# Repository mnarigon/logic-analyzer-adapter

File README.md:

## An S-100 Bus Logic Analyzer Adapter Board.

#### Description

This is an S-100 bus logic analyzer adapter board.
It simplifies the connection to the S-100 bus of common 40-pin pod cables like
those for older HP/Agilent/Keysight logic analyzers.

#### Features:
- Connectors and isolation networks for 40-pin pod cables.
- Oscilloscope test points for S-100 bus signals.
- Test points for logic analyzer clock inputs and unused channels.

See the Keysight document, [Probing Solutions for Logic Analyzers](https://www.keysight.com/us/en/assets/7018-06707/data-sheets/5968-4632.pdf),
for more information on the pod interface.

Note that the photo is of the prototype board.

The design files are revision A, and have some changes based on my experience
with the prototype board. I haven't had the revision A boards manufactured
since the prototype is working for my purposes.

#### Revision A Changes:
- Surface mount components moved to back of board to provide additional
connector clearance.
- Location of pod connectors adjusted to provide more clearance to each other
and to the card ejectors.
- Added test points for unassigned logic analyzer channels.
- Silkscreen for test points moved for visibility.

#### Logic Analyzer Adapter Design Files

The revision A logic analyzer adapter design files in KiCad 7 are in the kicad
directory.

The generated revision A logic analyzer adapter Gerber and drill files are in
the file la-adapter-gerbers.zip.

The bill of materials is in the bom directory.

#### Design Notes

The BOM calls out the 3M connectors described in the Keysight
document. There are probably cheaper, non-3M connectors that would work.

The design files define front and back gold layers to specify hard gold on
the S-100 bus card edge connector. Hard gold is expensive, and few prototype
board houses offer it, so for the prototype I just specified ENIG treatment
for the copper layers and card edge connector.

#### Hand-soldering the Capacitors and Resistors

I use a fine tip soldering iron (Weller with an ETU tip) together with tacky SMD
flux to apply a very light amount of solder to the component pads.
Remove excess solder by reheating with a clean soldering iron and/or using
solder removing wick.
You want just a small pillow of solder on each pad.
After the solder has cooled apply an additional, small amount of flux.
The flux will keep the components in position while they are being soldered with
the hot air rework station.

Then, position the component on the pads using an awl from a desoldering tool
set with a small amount of flux on it.
The tacky flux on the awl will let you transfer and position the component on
the board.

Finally, use a hot air rework station set at a low air velocity to reheat the
solder, flux, and component to solder the component to the board.
Too high an air velocity will blow off the component from the pads.
You can tell when the solder melts because the capillary action of the molten
solder will cause the component to align with the pads.
After the solder melts apply hot air for a slow count of five to ensure that
the flux activates and the solder wets the component and pad.

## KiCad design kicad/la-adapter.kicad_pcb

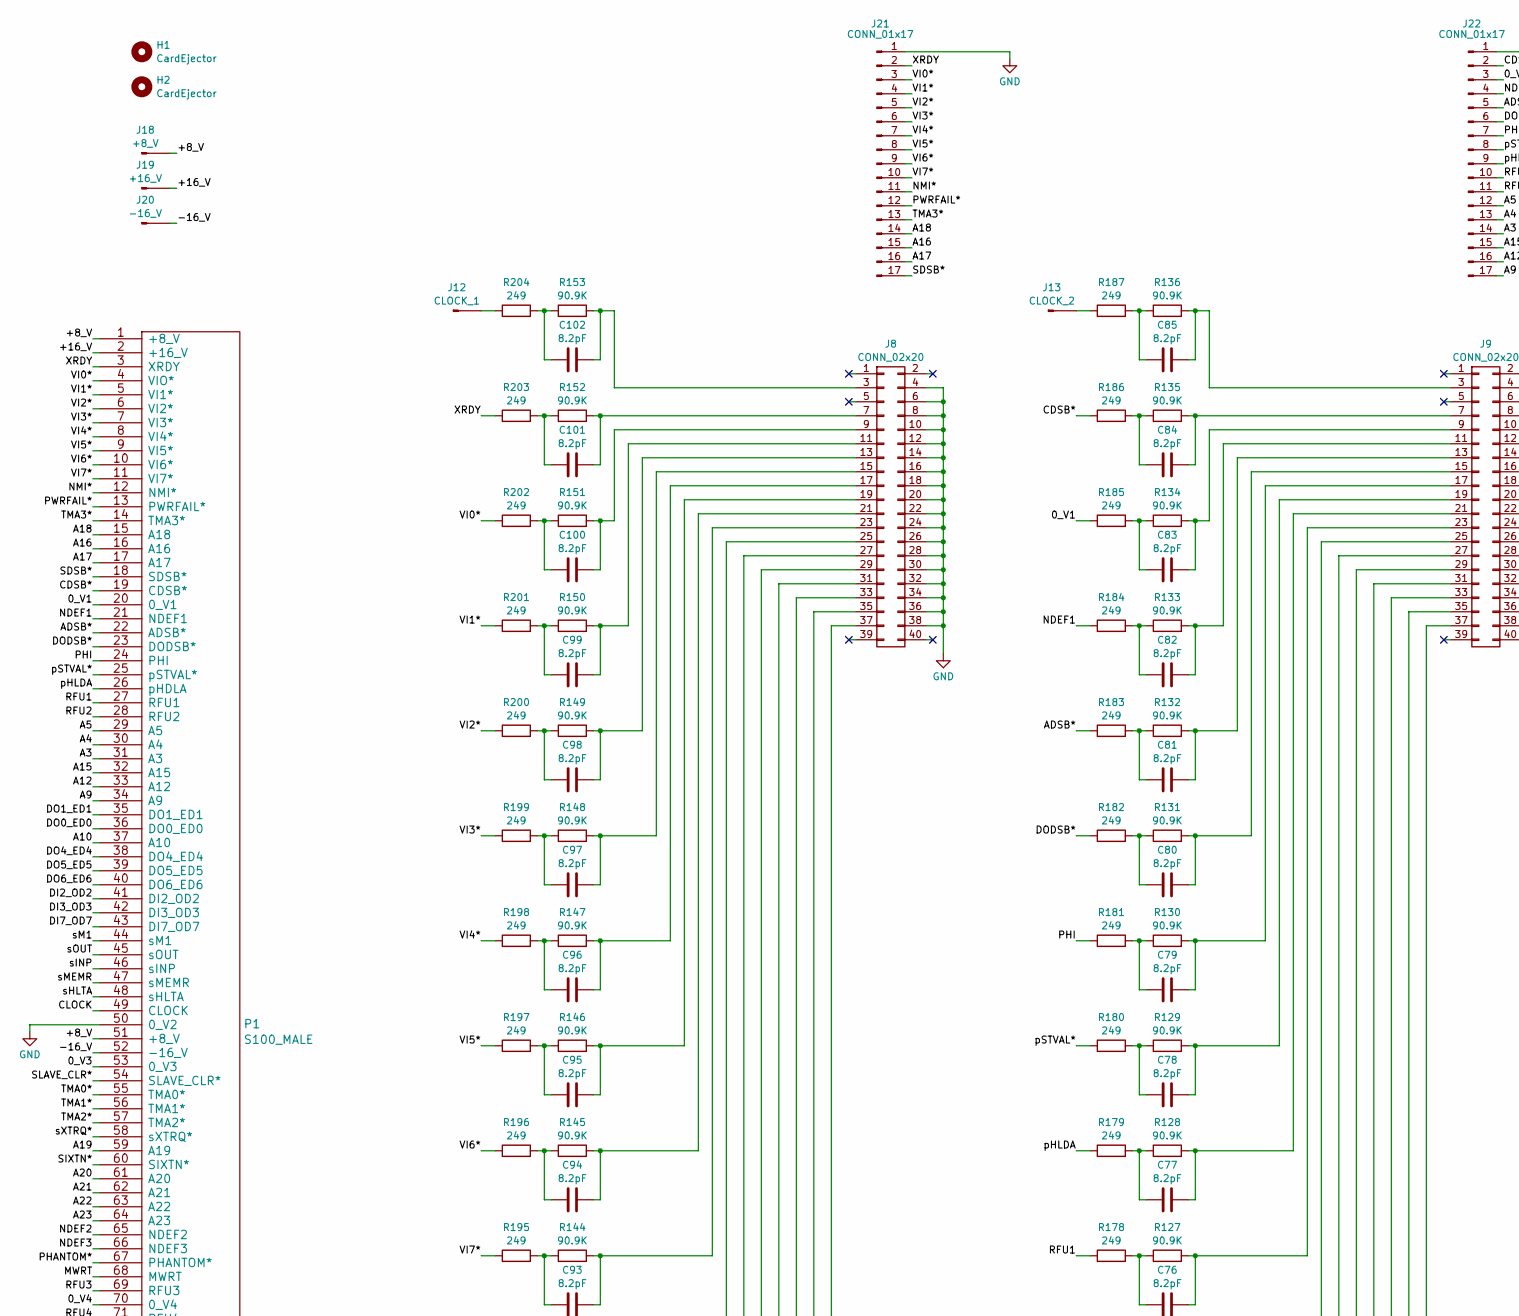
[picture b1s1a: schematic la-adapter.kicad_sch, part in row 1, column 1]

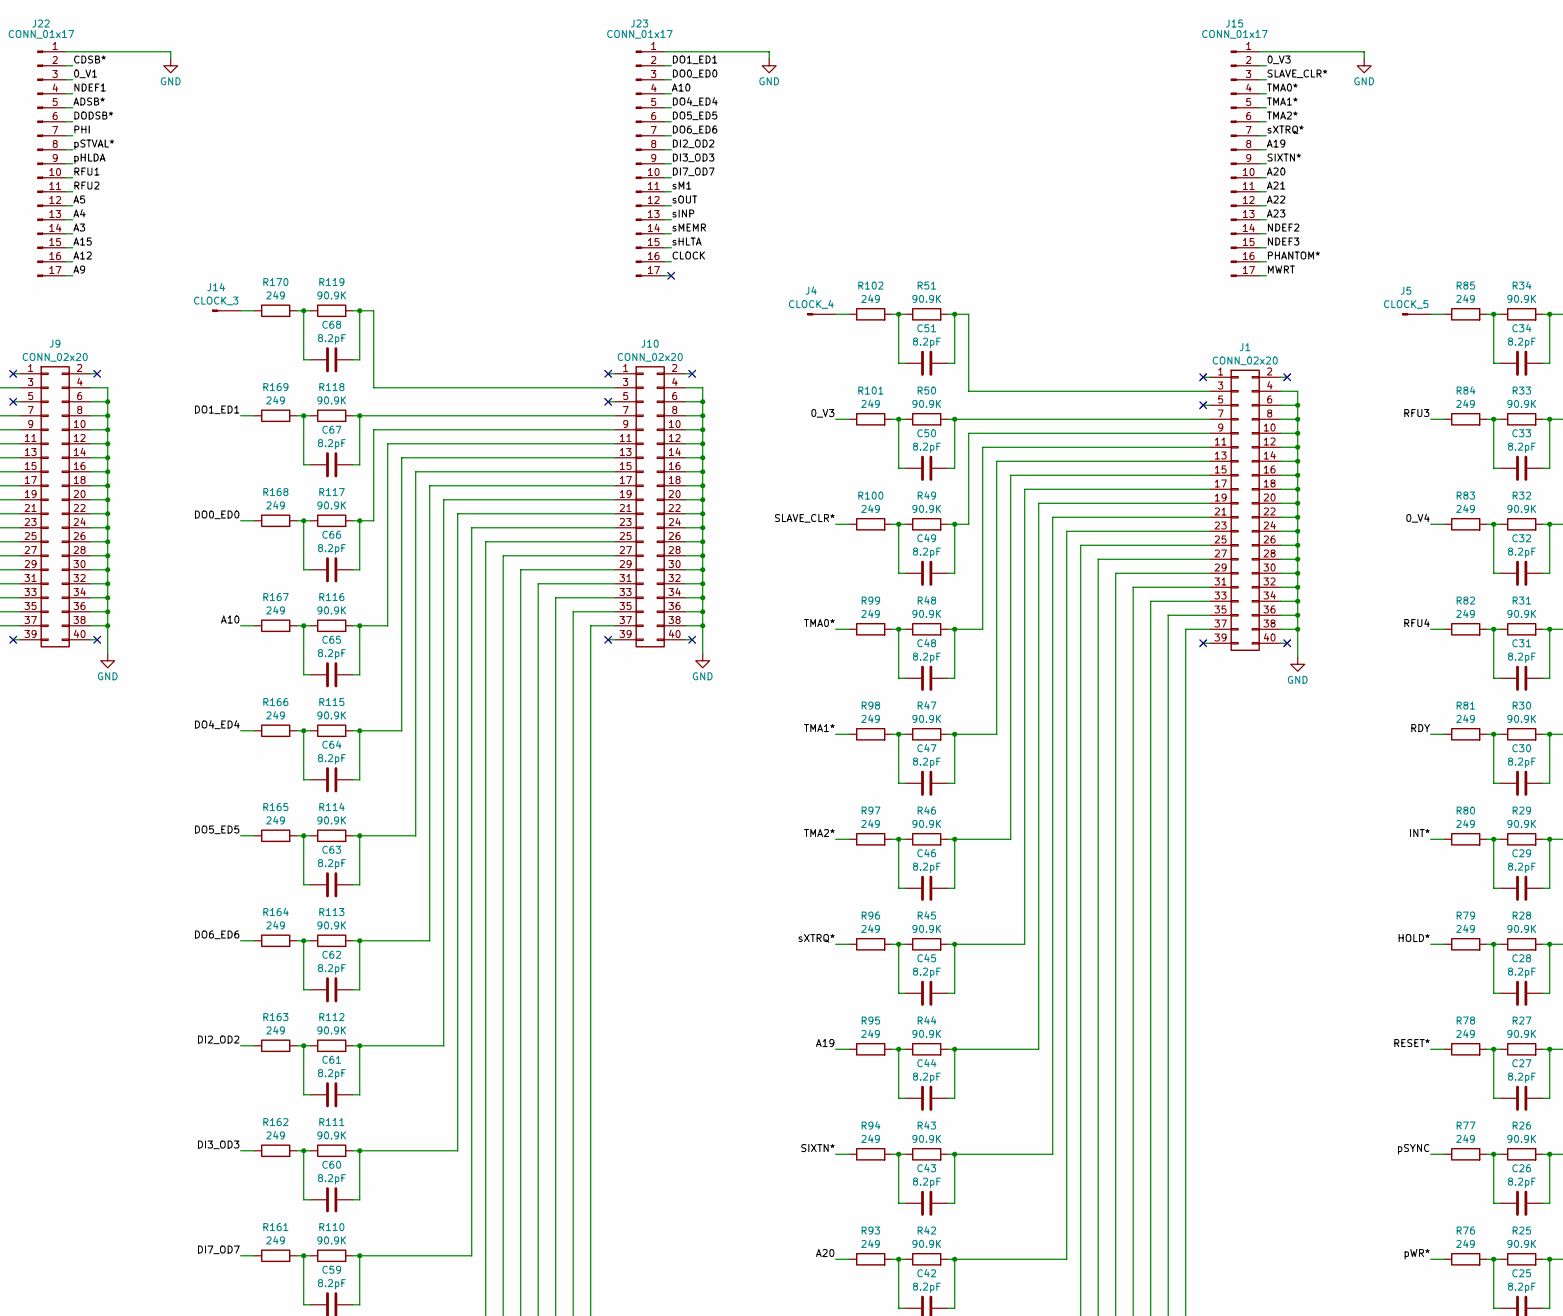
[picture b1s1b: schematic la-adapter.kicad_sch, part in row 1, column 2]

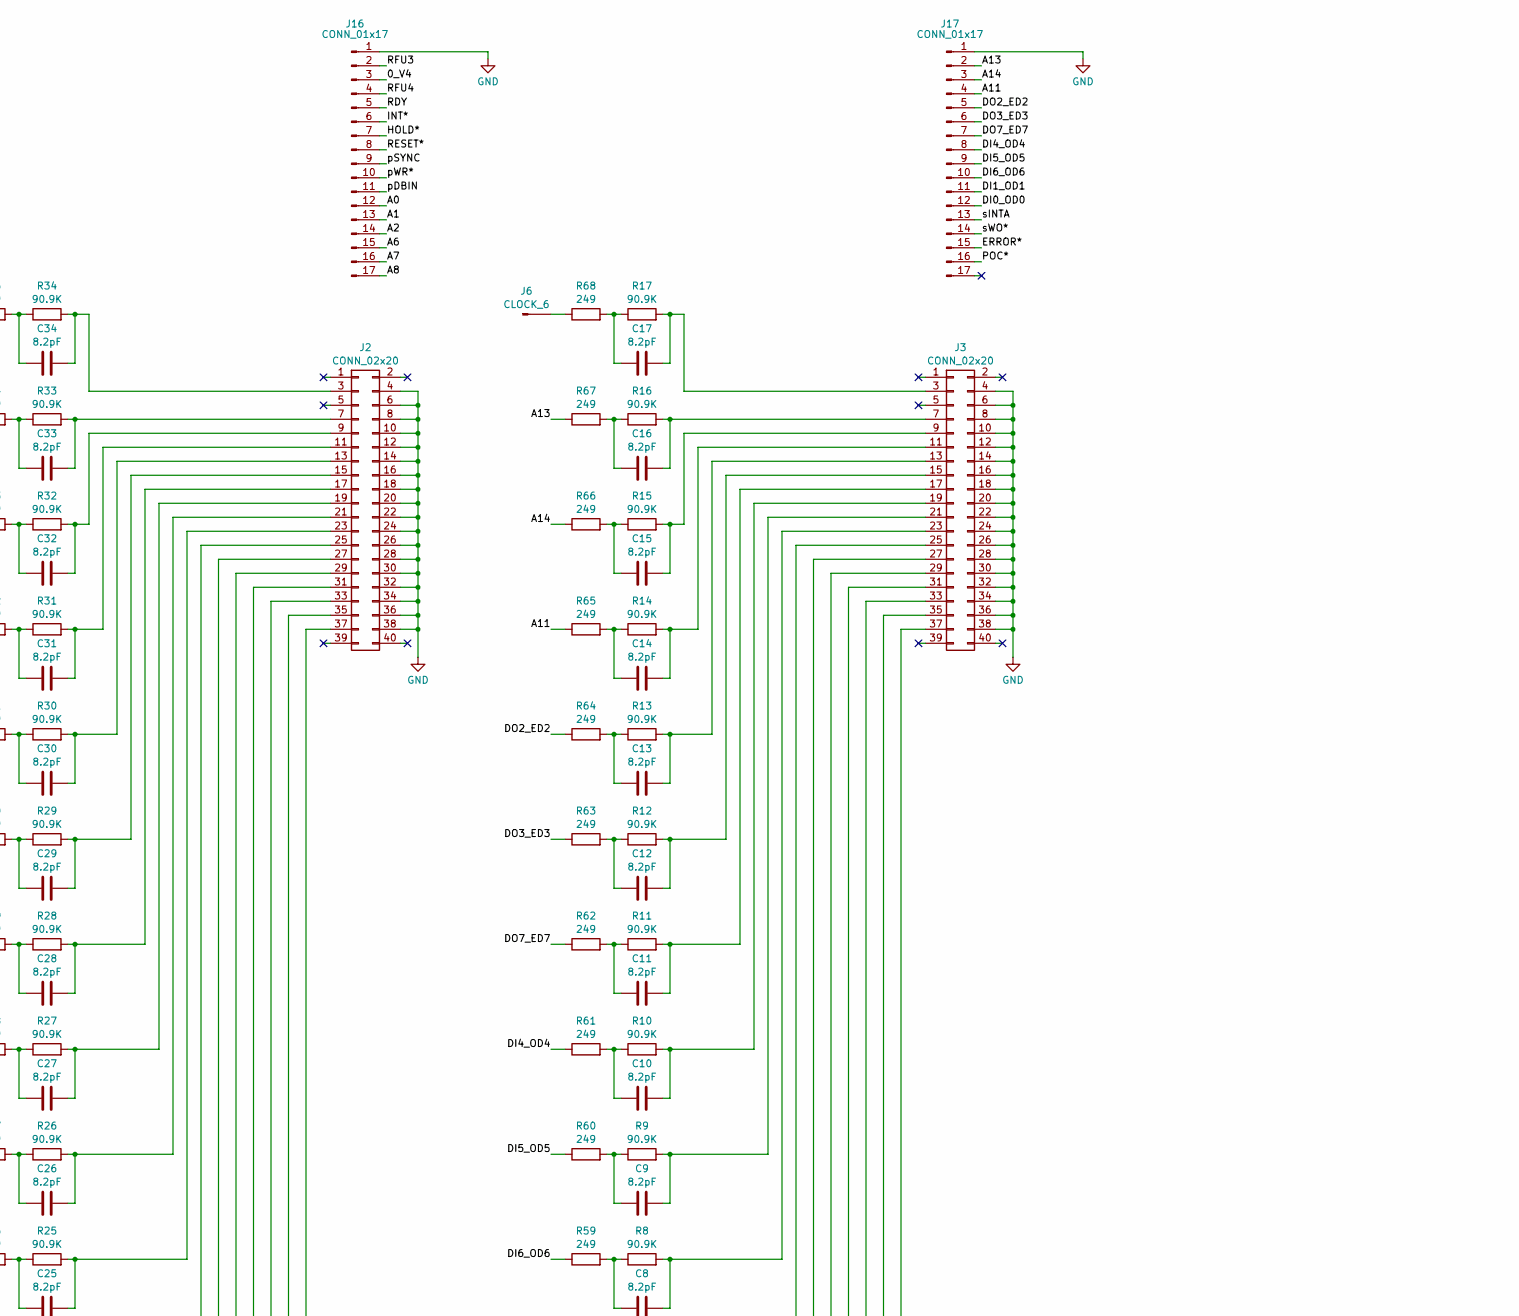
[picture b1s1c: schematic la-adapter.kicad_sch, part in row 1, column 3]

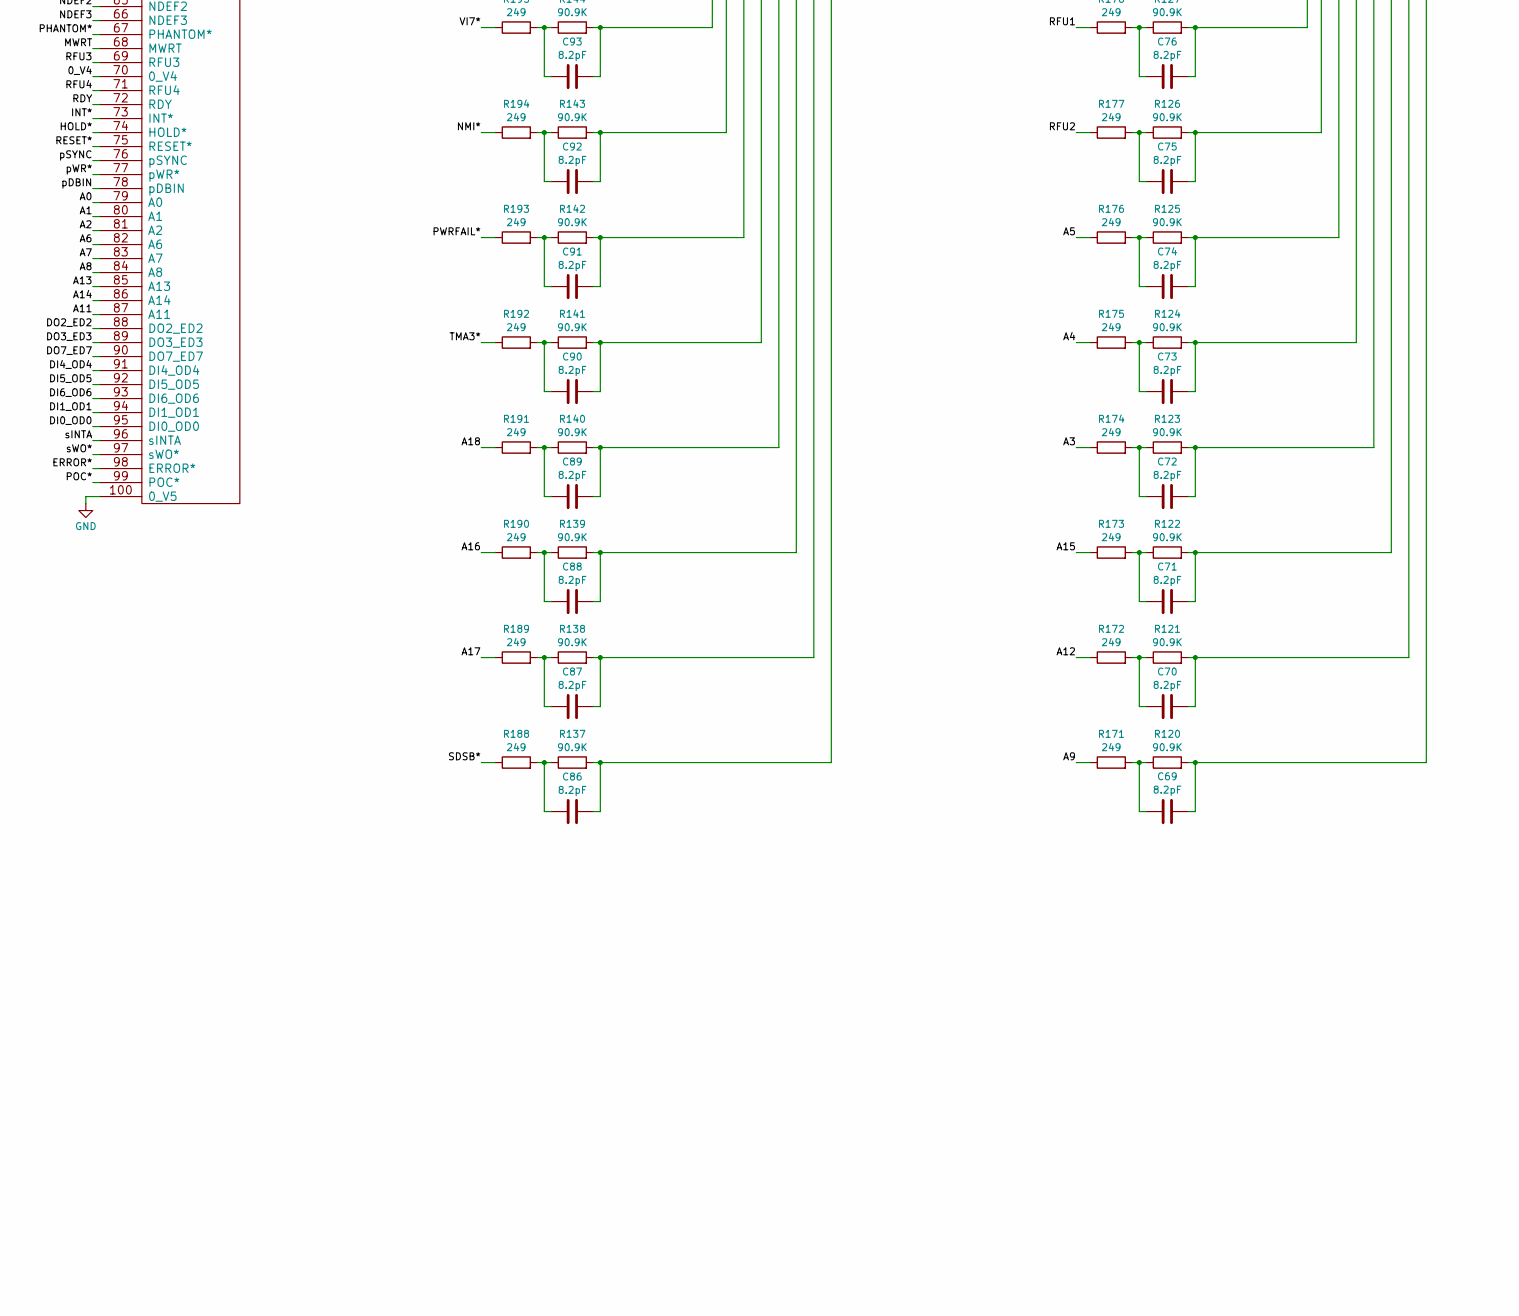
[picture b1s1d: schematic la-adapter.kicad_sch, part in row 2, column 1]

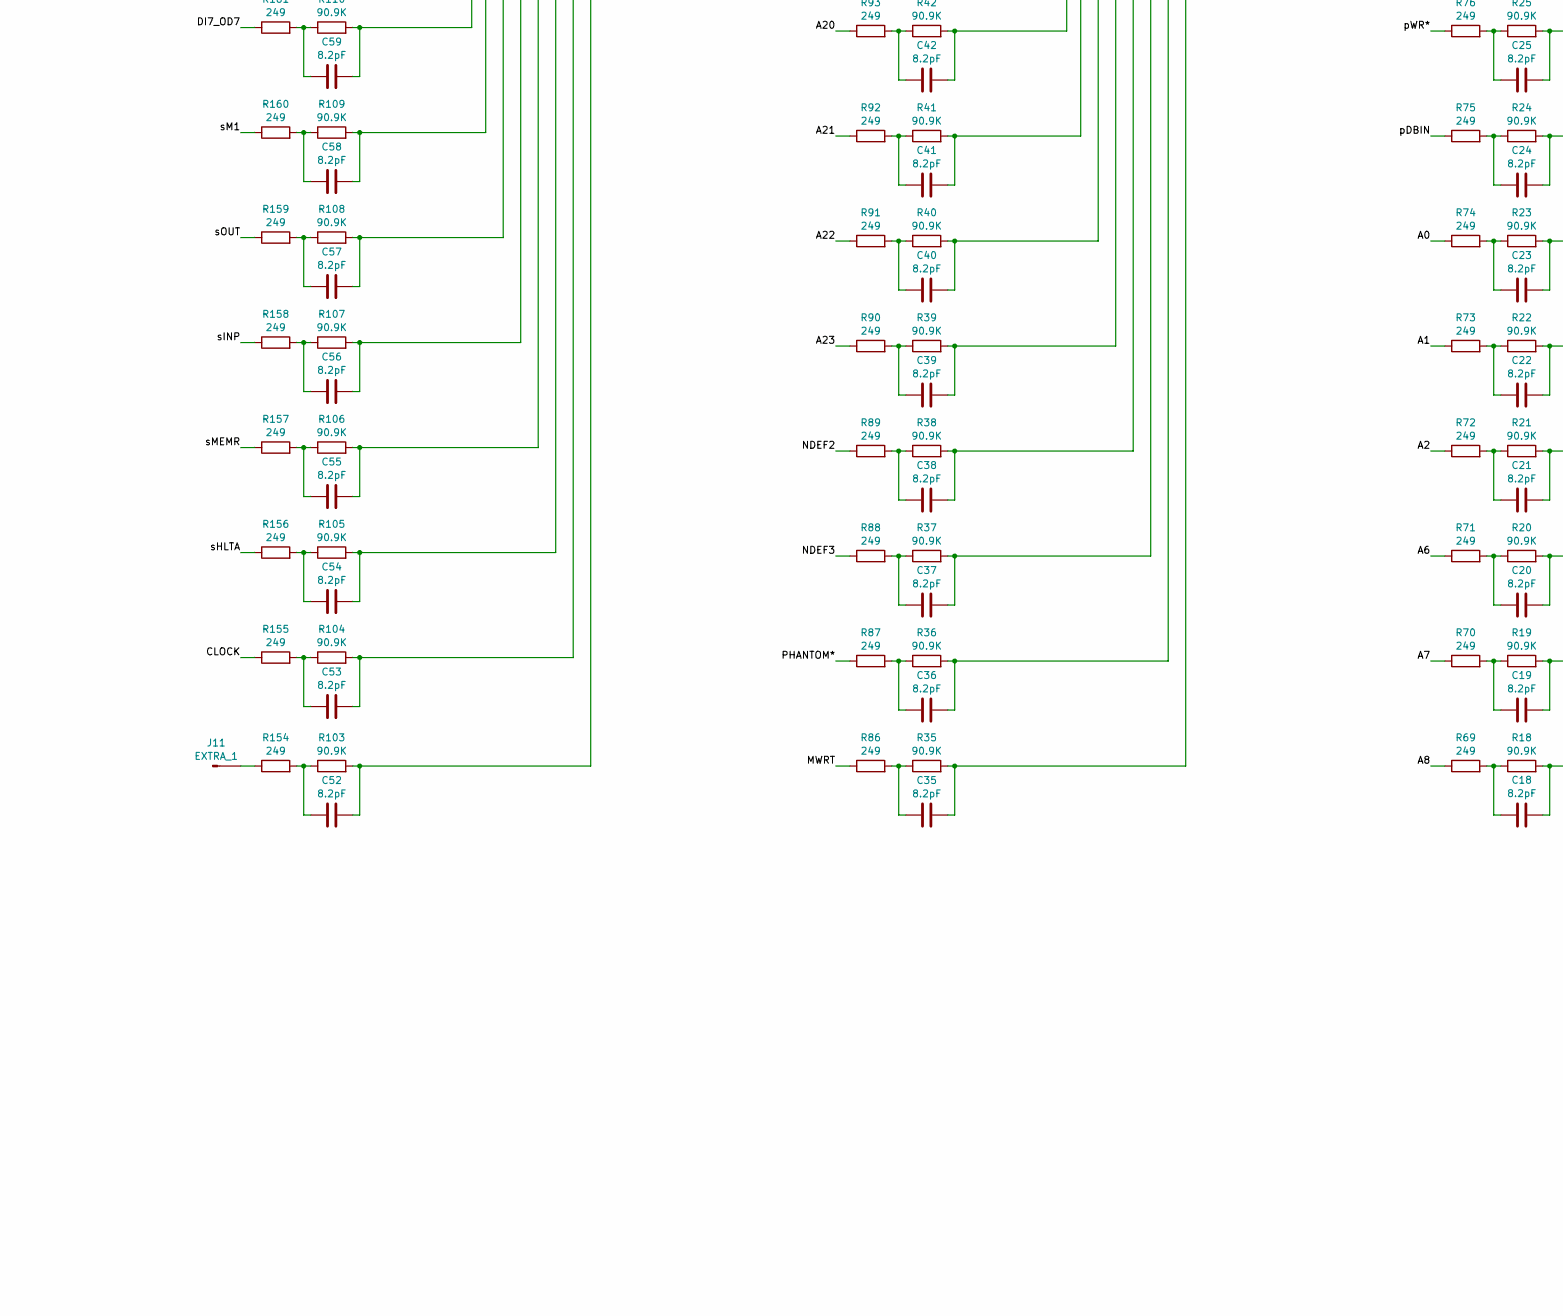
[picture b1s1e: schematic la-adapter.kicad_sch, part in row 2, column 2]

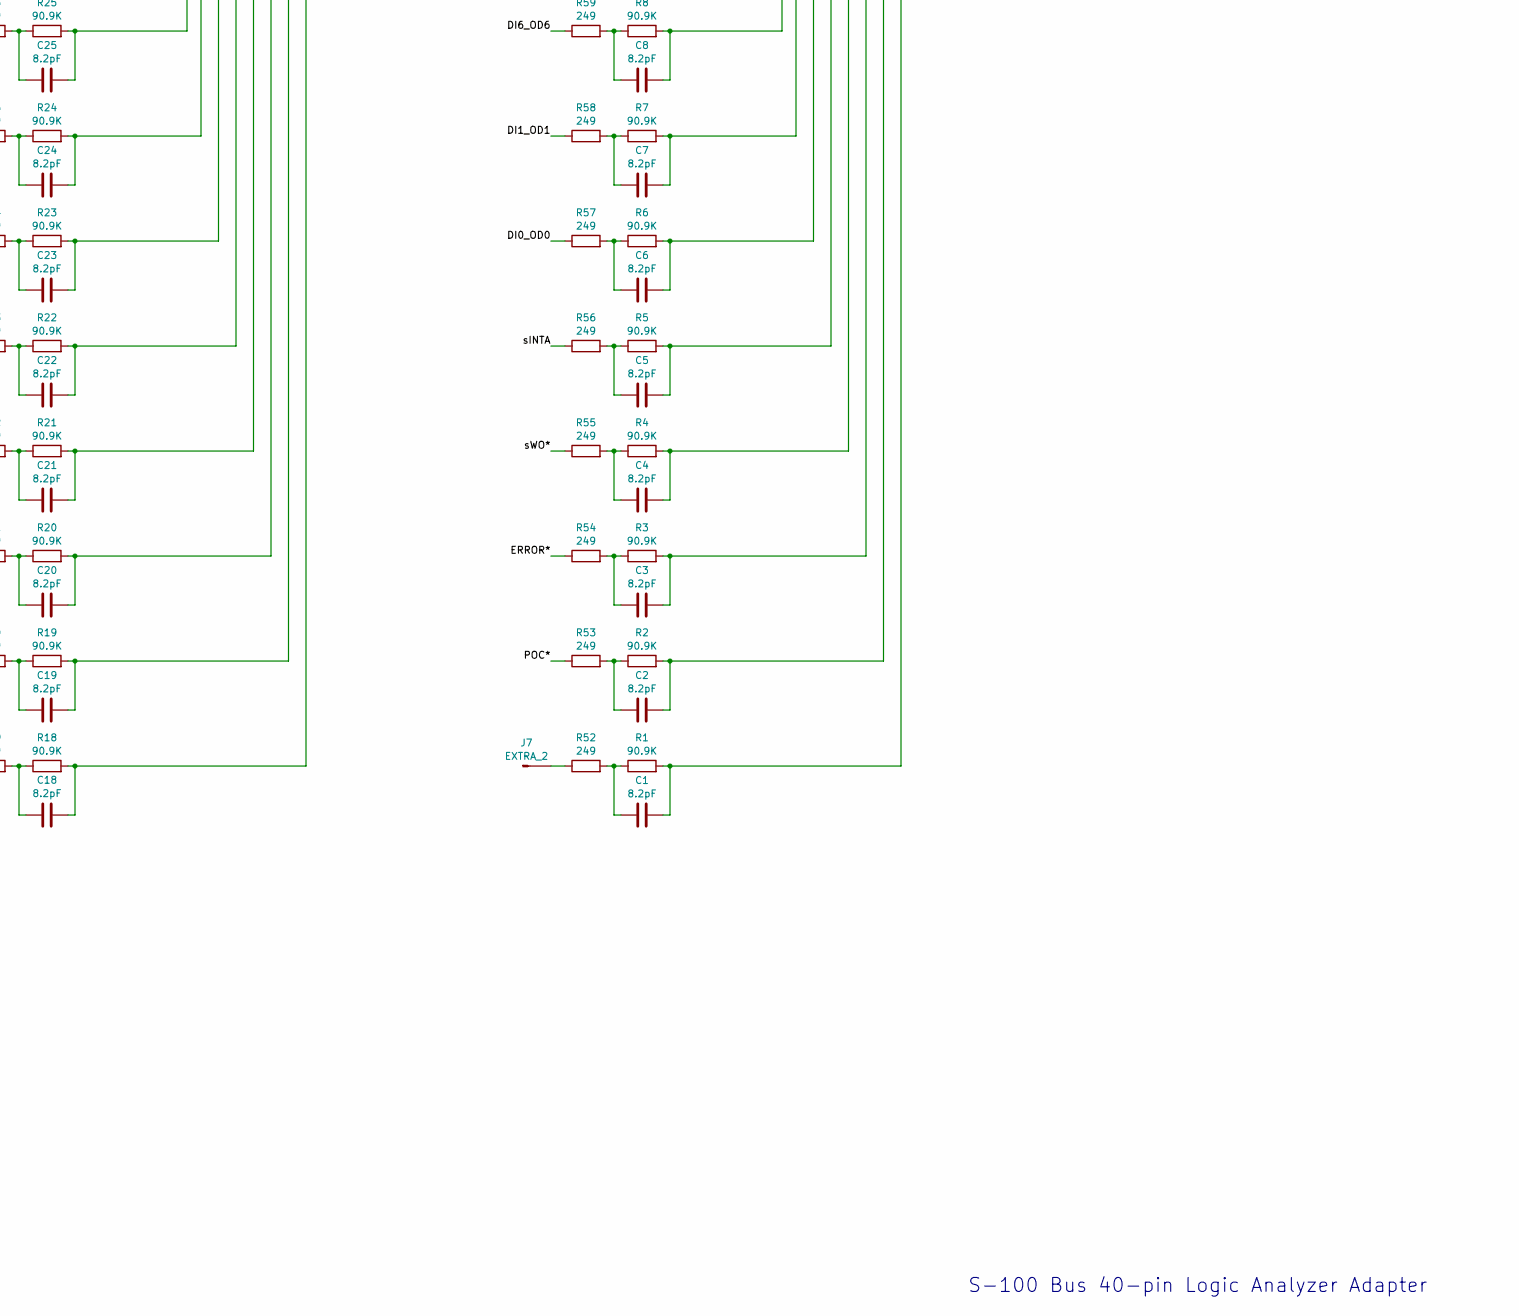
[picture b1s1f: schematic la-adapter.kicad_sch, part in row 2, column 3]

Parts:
C1, C2, C3, C4, C5, C6, C7, C8, C9, C10, C11, C12, C13, C14, C15, C16, C17, C18, C19, C20, C21, C22, C23, C24, C25, C26, C27, C28, C29, C30, C31, C32, C33, C34, C35, C36, C37, C38, C39, C40, C41, C42, C43, C44, C45, C46, C47, C48, C49, C50, C51, C52, C53, C54, C55, C56, C57, C58, C59, C60, C61, C62, C63, C64, C65, C66, C67, C68, C69, C70, C71, C72, C73, C74, C75, C76, C77, C78, C79, C80, C81, C82, C83, C84, C85, C86, C87, C88, C89, C90, C91, C92, C93, C94, C95, C96, C97, C98, C99, C100, C101, C102: 8.2pF; C_0805
H1, H2: CardEjector
J1, J2, J3, J8, J9, J10: CONN_02x20; IDC_Header_02x20_P2.54mm_RA
J4: CLOCK_4; PinHeader_01x01_P2.54mm_RA
J5: CLOCK_5; PinHeader_01x01_P2.54mm_RA
J6: CLOCK_6; PinHeader_01x01_P2.54mm_RA
J7: EXTRA_2; PinHeader_01x01_P2.54mm_RA
J11: EXTRA_1; PinHeader_01x01_P2.54mm_RA
J12: CLOCK_1; PinHeader_01x01_P2.54mm_RA
J13: CLOCK_2; PinHeader_01x01_P2.54mm_RA
J14: CLOCK_3; PinHeader_01x01_P2.54mm_RA
J15, J16, J17, J21, J22, J23: CONN_01x17; PinHeader_01x17_P2.54mm_RA
J18: +8_V; PinHeader_01x01_P2.54mm_RA
J19: +16_V; PinHeader_01x01_P2.54mm_RA
J20: -16_V; PinHeader_01x01_P2.54mm_RA
P1: S100_MALE
R1, R2, R3, R4, R5, R6, R7, R8, R9, R10, R11, R12, R13, R14, R15, R16, R17, R18, R19, R20, R21, R22, R23, R24, R25, R26, R27, R28, R29, R30, R31, R32, R33, R34, R35, R36, R37, R38, R39, R40, R41, R42, R43, R44, R45, R46, R47, R48, R49, R50, R51, R103, R104, R105, R106, R107, R108, R109, R110, R111, R112, R113, R114, R115, R116, R117, R118, R119, R120, R121, R122, R123, R124, R125, R126, R127, R128, R129, R130, R131, R132, R133, R134, R135, R136, R137, R138, R139, R140, R141, R142, R143, R144, R145, R146, R147, R148, R149, R150, R151, R152, R153: 90.9K; R_0805
R52, R53, R54, R55, R56, R57, R58, R59, R60, R61, R62, R63, R64, R65, R66, R67, R68, R69, R70, R71, R72, R73, R74, R75, R76, R77, R78, R79, R80, R81, R82, R83, R84, R85, R86, R87, R88, R89, R90, R91, R92, R93, R94, R95, R96, R97, R98, R99, R100, R101, R102, R154, R155, R156, R157, R158, R159, R160, R161, R162, R163, R164, R165, R166, R167, R168, R169, R170, R171, R172, R173, R174, R175, R176, R177, R178, R179, R180, R181, R182, R183, R184, R185, R186, R187, R188, R189, R190, R191, R192, R193, R194, R195, R196, R197, R198, R199, R200, R201, R202, R203, R204: 249; R_0805

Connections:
/0_V1: J22.3, P1.20 (0_V1), R185.1
/0_V3: J15.2, P1.53 (0_V3), R101.1
/0_V4: J16.3, P1.70 (0_V4), R83.1
/+8_V: J18.1, P1.1 (+8_V), P1.51 (+8_V)
/+16_V: J19.1, P1.2 (+16_V)
/-16_V: J20.1, P1.52 (-16_V)
/A0: J16.12, P1.79 (A0), R74.1
/A1: J16.13, P1.80 (A1), R73.1
/A2: J16.14, P1.81 (A2), R72.1
/A3: J22.14, P1.31 (A3), R174.1
/A4: J22.13, P1.30 (A4), R175.1
/A5: J22.12, P1.29 (A5), R176.1
/A6: J16.15, P1.82 (A6), R71.1
/A7: J16.16, P1.83 (A7), R70.1
/A8: J16.17, P1.84 (A8), R69.1
/A9: J22.17, P1.34 (A9), R171.1
/A10: J23.4, P1.37 (A10), R167.1
/A11: J17.4, P1.87 (A11), R65.1
/A12: J22.16, P1.33 (A12), R172.1
/A13: J17.2, P1.85 (A13), R67.1
/A14: J17.3, P1.86 (A14), R66.1
/A15: J22.15, P1.32 (A15), R173.1
/A16: J21.15, P1.16 (A16), R190.1
/A17: J21.16, P1.17 (A17), R189.1
/A18: J21.14, P1.15 (A18), R191.1
/A19: J15.8, P1.59 (A19), R95.1
/A20: J15.10, P1.61 (A20), R93.1
/A21: J15.11, P1.62 (A21), R92.1
/A22: J15.12, P1.63 (A22), R91.1
/A23: J15.13, P1.64 (A23), R90.1
/ADSB*: J22.5, P1.22 (ADSB*), R183.1
/CDSB*: J22.2, P1.19 (CDSB*), R186.1
/CLOCK: J23.16, P1.49 (CLOCK), R155.1
/DI0_OD0: J17.12, P1.95 (DI0_OD0), R57.1
/DI1_OD1: J17.11, P1.94 (DI1_OD1), R58.1
/DI2_OD2: J23.8, P1.41 (DI2_OD2), R163.1
/DI3_OD3: J23.9, P1.42 (DI3_OD3), R162.1
/DI4_OD4: J17.8, P1.91 (DI4_OD4), R61.1
/DI5_OD5: J17.9, P1.92 (DI5_OD5), R60.1
/DI6_OD6: J17.10, P1.93 (DI6_OD6), R59.1
/DI7_OD7: J23.10, P1.43 (DI7_OD7), R161.1
/DO0_ED0: J23.3, P1.36 (DO0_ED0), R168.1
/DO1_ED1: J23.2, P1.35 (DO1_ED1), R169.1
/DO2_ED2: J17.5, P1.88 (DO2_ED2), R64.1
/DO3_ED3: J17.6, P1.89 (DO3_ED3), R63.1
/DO4_ED4: J23.5, P1.38 (DO4_ED4), R166.1
/DO5_ED5: J23.6, P1.39 (DO5_ED5), R165.1
/DO6_ED6: J23.7, P1.40 (DO6_ED6), R164.1
/DO7_ED7: J17.7, P1.90 (DO7_ED7), R62.1
/DODSB*: J22.6, P1.23 (DODSB*), R182.1
/ERROR*: J17.15, P1.98 (ERROR*), R54.1
/HOLD*: J16.7, P1.74 (HOLD*), R79.1
/INT*: J16.6, P1.73 (INT*), R80.1
/MWRT: J15.17, P1.68 (MWRT), R86.1
/NDEF1: J22.4, P1.21 (NDEF1), R184.1
/NDEF2: J15.14, P1.65 (NDEF2), R89.1
/NDEF3: J15.15, P1.66 (NDEF3), R88.1
/NMI*: J21.11, P1.12 (NMI*), R194.1
/PHANTOM*: J15.16, P1.67 (PHANTOM*), R87.1
/PHI: J22.7, P1.24 (PHI), R181.1
/POC*: J17.16, P1.99 (POC*), R53.1
/PWRFAIL*: J21.12, P1.13 (PWRFAIL*), R193.1
/RDY: J16.5, P1.72 (RDY), R81.1
/RESET*: J16.8, P1.75 (RESET*), R78.1
/RFU1: J22.10, P1.27 (RFU1), R178.1
/RFU2: J22.11, P1.28 (RFU2), R177.1
/RFU3: J16.2, P1.69 (RFU3), R84.1
/RFU4: J16.4, P1.71 (RFU4), R82.1
/SDSB*: J21.17, P1.18 (SDSB*), R188.1
/SIXTN*: J15.9, P1.60 (SIXTN*), R94.1
/SLAVE_CLR*: J15.3, P1.54 (SLAVE_CLR*), R100.1
/TMA0*: J15.4, P1.55 (TMA0*), R99.1
/TMA1*: J15.5, P1.56 (TMA1*), R98.1
/TMA2*: J15.6, P1.57 (TMA2*), R97.1
/TMA3*: J21.13, P1.14 (TMA3*), R192.1
/VI0*: J21.3, P1.4 (VIO*), R202.1
/VI1*: J21.4, P1.5 (VI1*), R201.1
/VI2*: J21.5, P1.6 (VI2*), R200.1
/VI3*: J21.6, P1.7 (VI3*), R199.1
/VI4*: J21.7, P1.8 (VI4*), R198.1
/VI5*: J21.8, P1.9 (VI5*), R197.1
/VI6*: J21.9, P1.10 (VI6*), R196.1
/VI7*: J21.10, P1.11 (VI7*), R195.1
/XRDY: J21.2, P1.3 (XRDY), R203.1
/pDBIN: J16.11, P1.78 (pDBIN), R75.1
/pHLDA: J22.9, P1.26 (pHDLA), R179.1
/pSTVAL*: J22.8, P1.25 (pSTVAL*), R180.1
/pSYNC: J16.9, P1.76 (pSYNC), R77.1
/pWR*: J16.10, P1.77 (pWR*), R76.1
/sHLTA: J23.15, P1.48 (sHLTA), R156.1
/sINP: J23.13, P1.46 (sINP), R158.1
/sINTA: J17.13, P1.96 (sINTA), R56.1
/sM1: J23.11, P1.44 (sM1), R160.1
/sMEMR: J23.14, P1.47 (sMEMR), R157.1
/sOUT: J23.12, P1.45 (sOUT), R159.1
/sWO*: J17.14, P1.97 (sWO*), R55.1
/sXTRQ*: J15.7, P1.58 (sXTRQ*), R96.1
GND: J1.4, J1.6, J1.8, J1.10, J1.12, J1.14, J1.16, J1.18, J1.20, J1.22, J1.24, J1.26, J1.28, J1.30, J1.32, J1.34, J1.36, J1.38, J2.4, J2.6, J2.8, J2.10, J2.12, J2.14, J2.16, J2.18, J2.20, J2.22, J2.24, J2.26, J2.28, J2.30, J2.32, J2.34, J2.36, J2.38, J3.4, J3.6, J3.8, J3.10, J3.12, J3.14, J3.16, J3.18, J3.20, J3.22, J3.24, J3.26, J3.28, J3.30, J3.32, J3.34, J3.36, J3.38, J8.4, J8.6, J8.8, J8.10, J8.12, J8.14, J8.16, J8.18, J8.20, J8.22, J8.24, J8.26, J8.28, J8.30, J8.32, J8.34, J8.36, J8.38, J9.4, J9.6, J9.8, J9.10, J9.12, J9.14, J9.16, J9.18, J9.20, J9.22, J9.24, J9.26, J9.28, J9.30, J9.32, J9.34, J9.36, J9.38, J10.4, J10.6, J10.8, J10.10, J10.12, J10.14, J10.16, J10.18, J10.20, J10.22, J10.24, J10.26, J10.28, J10.30, J10.32, J10.34, J10.36, J10.38, J15.1, J16.1, J17.1, J21.1, J22.1, J23.1, P1.50 (0_V2), P1.100 (0_V5)
unnamed: C1.1, R1.1, R52.2
unnamed: C2.1, R2.1, R53.2
unnamed: C3.1, R3.1, R54.2
unnamed: C4.1, R4.1, R55.2
unnamed: C5.1, R5.1, R56.2
unnamed: C6.1, R6.1, R57.2
unnamed: C7.1, R7.1, R58.2
unnamed: C8.1, R8.1, R59.2
unnamed: C9.1, R9.1, R60.2
unnamed: C10.1, R10.1, R61.2
unnamed: C11.1, R11.1, R62.2
unnamed: C12.1, R12.1, R63.2
unnamed: C13.1, R13.1, R64.2
unnamed: C14.1, R14.1, R65.2
unnamed: C15.1, R15.1, R66.2
unnamed: C16.1, R16.1, R67.2
unnamed: C17.1, R17.1, R68.2
unnamed: C18.1, R18.1, R69.2
unnamed: C19.1, R19.1, R70.2
unnamed: C20.1, R20.1, R71.2
unnamed: C21.1, R21.1, R72.2
unnamed: C22.1, R22.1, R73.2
unnamed: C23.1, R23.1, R74.2
unnamed: C24.1, R24.1, R75.2
unnamed: C25.1, R25.1, R76.2
unnamed: C26.1, R26.1, R77.2
unnamed: C27.1, R27.1, R78.2
unnamed: C28.1, R28.1, R79.2
unnamed: C29.1, R29.1, R80.2
unnamed: C30.1, R30.1, R81.2
unnamed: C31.1, R31.1, R82.2
unnamed: C32.1, R32.1, R83.2
unnamed: C33.1, R33.1, R84.2
unnamed: C34.1, R34.1, R85.2
unnamed: C35.1, R35.1, R86.2
unnamed: C36.1, R36.1, R87.2
unnamed: C37.1, R37.1, R88.2
unnamed: C38.1, R38.1, R89.2
unnamed: C39.1, R39.1, R90.2
unnamed: C40.1, R40.1, R91.2
unnamed: C41.1, R41.1, R92.2
unnamed: C42.1, R42.1, R93.2
unnamed: C43.1, R43.1, R94.2
unnamed: C44.1, R44.1, R95.2
unnamed: C45.1, R45.1, R96.2
unnamed: C46.1, R46.1, R97.2
unnamed: C47.1, R47.1, R98.2
unnamed: C48.1, R48.1, R99.2
unnamed: C49.1, R49.1, R100.2
unnamed: C50.1, R50.1, R101.2
unnamed: C51.1, R51.1, R102.2
unnamed: C52.1, R103.1, R154.2
unnamed: C53.1, R104.1, R155.2
unnamed: C54.1, R105.1, R156.2
unnamed: C55.1, R106.1, R157.2
unnamed: C56.1, R107.1, R158.2
unnamed: C57.1, R108.1, R159.2
unnamed: C58.1, R109.1, R160.2
unnamed: C59.1, R110.1, R161.2
unnamed: C60.1, R111.1, R162.2
unnamed: C61.1, R112.1, R163.2
unnamed: C62.1, R113.1, R164.2
unnamed: C63.1, R114.1, R165.2
unnamed: C64.1, R115.1, R166.2
unnamed: C65.1, R116.1, R167.2
unnamed: C66.1, R117.1, R168.2
unnamed: C67.1, R118.1, R169.2
unnamed: C68.1, R119.1, R170.2
unnamed: C69.1, R120.1, R171.2
unnamed: C70.1, R121.1, R172.2
unnamed: C71.1, R122.1, R173.2
unnamed: C72.1, R123.1, R174.2
unnamed: C73.1, R124.1, R175.2
unnamed: C74.1, R125.1, R176.2
unnamed: C75.1, R126.1, R177.2
unnamed: C76.1, R127.1, R178.2
unnamed: C77.1, R128.1, R179.2
unnamed: C78.1, R129.1, R180.2
unnamed: C79.1, R130.1, R181.2
unnamed: C80.1, R131.1, R182.2
unnamed: C81.1, R132.1, R183.2
unnamed: C82.1, R133.1, R184.2
unnamed: C83.1, R134.1, R185.2
unnamed: C84.1, R135.1, R186.2
unnamed: C85.1, R136.1, R187.2
unnamed: C86.1, R137.1, R188.2
unnamed: C87.1, R138.1, R189.2
unnamed: C88.1, R139.1, R190.2
unnamed: C89.1, R140.1, R191.2
unnamed: C90.1, R141.1, R192.2
unnamed: C91.1, R142.1, R193.2
unnamed: C92.1, R143.1, R194.2
unnamed: C93.1, R144.1, R195.2
unnamed: C94.1, R145.1, R196.2
unnamed: C95.1, R146.1, R197.2
unnamed: C96.1, R147.1, R198.2
unnamed: C97.1, R148.1, R199.2
unnamed: C98.1, R149.1, R200.2
unnamed: C99.1, R150.1, R201.2
unnamed: C100.1, R151.1, R202.2
unnamed: C101.1, R152.1, R203.2
unnamed: C102.1, R153.1, R204.2
unnamed: C51.2, J1.3, R51.2
unnamed: C50.2, J1.7, R50.2
unnamed: C49.2, J1.9, R49.2
unnamed: C48.2, J1.11, R48.2
unnamed: C47.2, J1.13, R47.2
unnamed: C46.2, J1.15, R46.2
unnamed: C45.2, J1.17, R45.2
unnamed: C44.2, J1.19, R44.2
unnamed: C43.2, J1.21, R43.2
unnamed: C42.2, J1.23, R42.2
unnamed: C41.2, J1.25, R41.2
unnamed: C40.2, J1.27, R40.2
unnamed: C39.2, J1.29, R39.2
unnamed: C38.2, J1.31, R38.2
unnamed: C37.2, J1.33, R37.2
unnamed: C36.2, J1.35, R36.2
unnamed: C35.2, J1.37, R35.2
unnamed: C34.2, J2.3, R34.2
unnamed: C33.2, J2.7, R33.2
unnamed: C32.2, J2.9, R32.2
unnamed: C31.2, J2.11, R31.2
unnamed: C30.2, J2.13, R30.2
unnamed: C29.2, J2.15, R29.2
unnamed: C28.2, J2.17, R28.2
unnamed: C27.2, J2.19, R27.2
unnamed: C26.2, J2.21, R26.2
unnamed: C25.2, J2.23, R25.2
unnamed: C24.2, J2.25, R24.2
unnamed: C23.2, J2.27, R23.2
unnamed: C22.2, J2.29, R22.2
unnamed: C21.2, J2.31, R21.2
unnamed: C20.2, J2.33, R20.2
unnamed: C19.2, J2.35, R19.2
unnamed: C18.2, J2.37, R18.2
unnamed: C17.2, J3.3, R17.2
unnamed: C16.2, J3.7, R16.2
unnamed: C15.2, J3.9, R15.2
unnamed: C14.2, J3.11, R14.2
unnamed: C13.2, J3.13, R13.2
unnamed: C12.2, J3.15, R12.2
unnamed: C11.2, J3.17, R11.2
unnamed: C10.2, J3.19, R10.2
unnamed: C9.2, J3.21, R9.2
unnamed: C8.2, J3.23, R8.2
unnamed: C7.2, J3.25, R7.2
unnamed: C6.2, J3.27, R6.2
unnamed: C5.2, J3.29, R5.2
unnamed: C4.2, J3.31, R4.2
unnamed: C3.2, J3.33, R3.2
unnamed: C2.2, J3.35, R2.2
unnamed: C1.2, J3.37, R1.2
unnamed: J4.1, R102.1
unnamed: J5.1, R85.1
unnamed: J6.1, R68.1
unnamed: J7.1, R52.1
unnamed: C102.2, J8.3, R153.2
unnamed: C101.2, J8.7, R152.2
unnamed: C100.2, J8.9, R151.2
unnamed: C99.2, J8.11, R150.2
unnamed: C98.2, J8.13, R149.2
unnamed: C97.2, J8.15, R148.2
unnamed: C96.2, J8.17, R147.2
unnamed: C95.2, J8.19, R146.2
unnamed: C94.2, J8.21, R145.2
unnamed: C93.2, J8.23, R144.2
unnamed: C92.2, J8.25, R143.2
unnamed: C91.2, J8.27, R142.2
unnamed: C90.2, J8.29, R141.2
unnamed: C89.2, J8.31, R140.2
unnamed: C88.2, J8.33, R139.2
unnamed: C87.2, J8.35, R138.2
unnamed: C86.2, J8.37, R137.2
unnamed: C85.2, J9.3, R136.2
unnamed: C84.2, J9.7, R135.2
unnamed: C83.2, J9.9, R134.2
unnamed: C82.2, J9.11, R133.2
unnamed: C81.2, J9.13, R132.2
unnamed: C80.2, J9.15, R131.2
unnamed: C79.2, J9.17, R130.2
unnamed: C78.2, J9.19, R129.2
unnamed: C77.2, J9.21, R128.2
unnamed: C76.2, J9.23, R127.2
unnamed: C75.2, J9.25, R126.2
unnamed: C74.2, J9.27, R125.2
unnamed: C73.2, J9.29, R124.2
unnamed: C72.2, J9.31, R123.2
unnamed: C71.2, J9.33, R122.2
unnamed: C70.2, J9.35, R121.2
unnamed: C69.2, J9.37, R120.2
unnamed: C68.2, J10.3, R119.2
unnamed: C67.2, J10.7, R118.2
unnamed: C66.2, J10.9, R117.2
unnamed: C65.2, J10.11, R116.2
unnamed: C64.2, J10.13, R115.2
unnamed: C63.2, J10.15, R114.2
unnamed: C62.2, J10.17, R113.2
unnamed: C61.2, J10.19, R112.2
unnamed: C60.2, J10.21, R111.2
unnamed: C59.2, J10.23, R110.2
unnamed: C58.2, J10.25, R109.2
unnamed: C57.2, J10.27, R108.2
unnamed: C56.2, J10.29, R107.2
unnamed: C55.2, J10.31, R106.2
unnamed: C54.2, J10.33, R105.2
unnamed: C53.2, J10.35, R104.2
unnamed: C52.2, J10.37, R103.2
unnamed: J11.1, R154.1
unnamed: J12.1, R204.1
unnamed: J13.1, R187.1
unnamed: J14.1, R170.1

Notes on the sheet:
S-100 Bus 40-pin Logic Analyzer Adapter

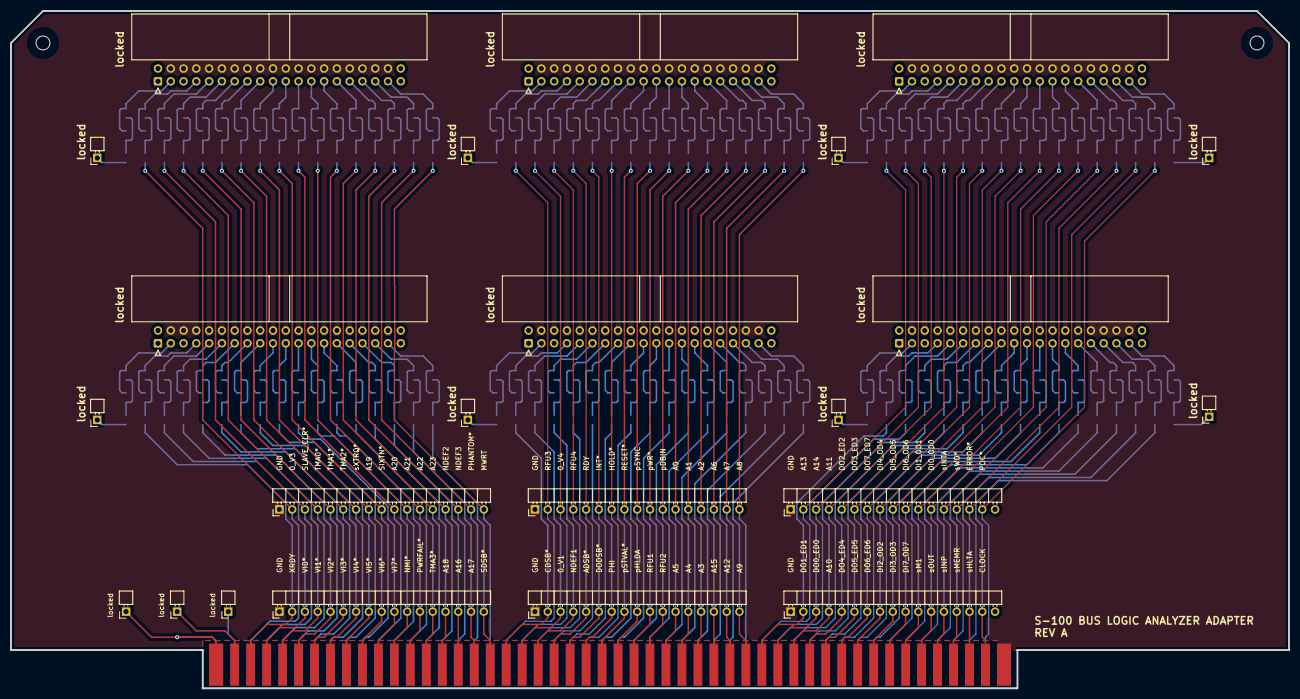
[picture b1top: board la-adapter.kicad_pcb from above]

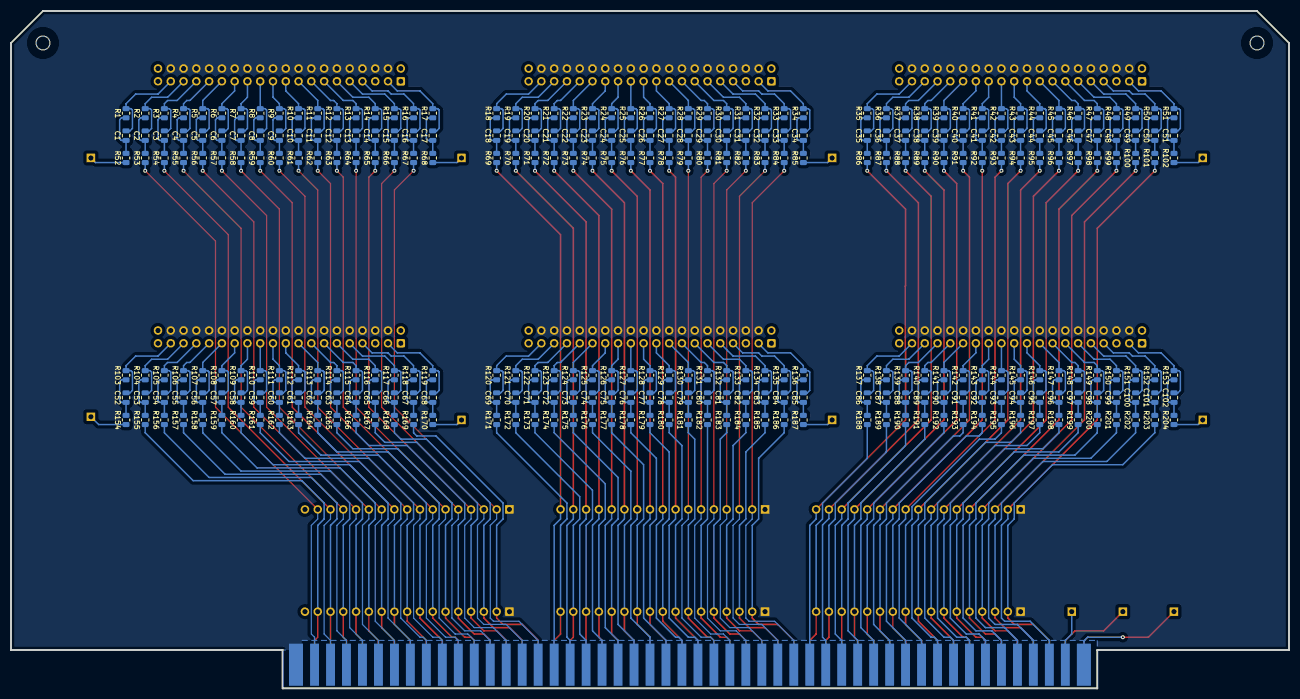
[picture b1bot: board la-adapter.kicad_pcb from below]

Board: 2 copper layers, 254.0 x 134.6 mm, 332 parts (306 on the bottom side), 310 nets.

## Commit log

2023-12-26 reorganized repository
2023-12-27 additional notes
